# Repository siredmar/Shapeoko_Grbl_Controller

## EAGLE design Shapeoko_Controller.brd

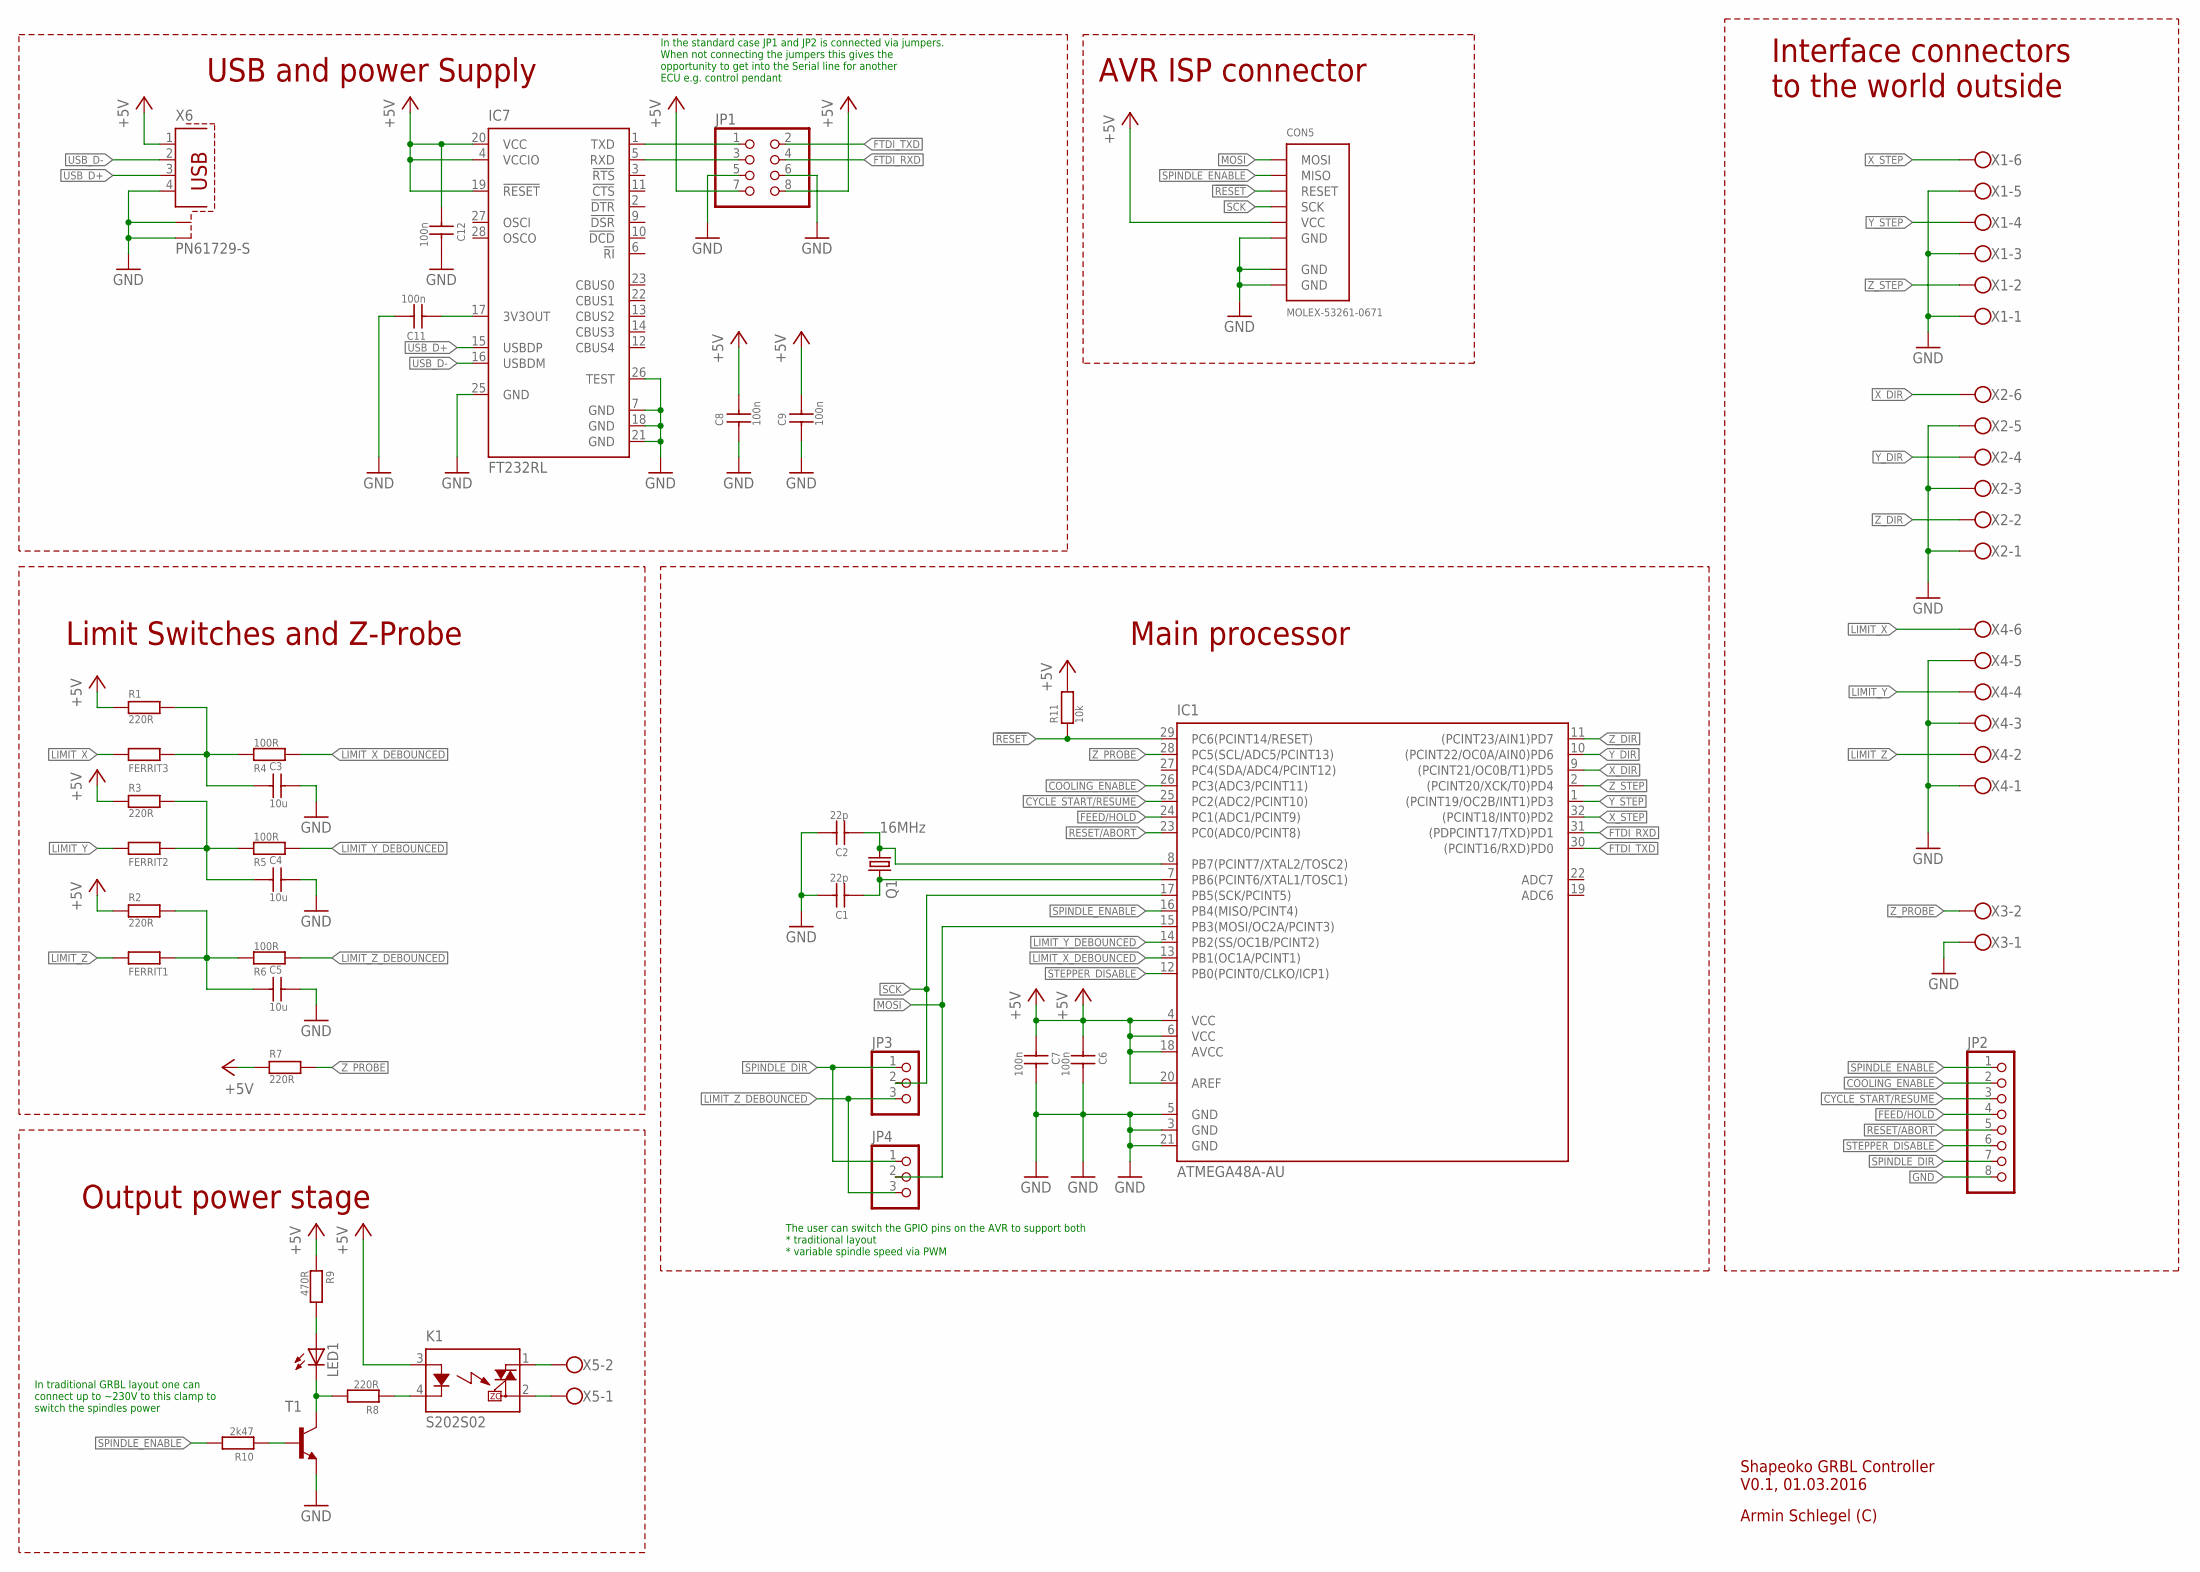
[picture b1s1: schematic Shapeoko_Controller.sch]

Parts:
C1, C2: 22p; C0603
C3, C4, C5: 10u; C0805
C6, C7, C8, C9, C11, C12: 100n; C0603
CON5: MOLEX-53261-0671
FERRIT1, FERRIT2, FERRIT3: R0805
IC1: ATMEGA48A-AU; TQFP32
IC7: FT232RL; SSOP28
JP1: PINHD-2X4; 2X04
JP2: PINHD-1X8; 1X08
JP3, JP4: PINHD-1X3; 1X03
K1: S202S02
LED1: LED3MM
Q1: 16MHz; HC49UP
R1, R2, R3, R7, R8: 220R; R0603
R4, R5, R6: 100R; R0603
R9: 470R; R0603
R10: 2k47; R0603
R11: 10k; R0603
T1: BC847-NPN-SOT23-BEC; SOT23-BEC
X1, X2, X4: W237-136
X3, X5: W237-102
X6: PN61729-S

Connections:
!RESET: CON5.3 (RESET), IC1.29 (PC6(PCINT14/RESET)), R11.1
+5V: C6.1, C7.1, C8.2, C9.2, C12.1, CON5.5 (VCC), IC1.4 (VCC), IC1.6 (VCC), IC1.18 (AVCC), IC1.20 (AREF), IC7.4 (VCCIO), IC7.19 (!RESET), IC7.20 (VCC), JP1.7, JP1.8, K1.3 (A), R1.1, R2.1, R3.1, R7.1, R9.1, R11.2, X6.1
COOLING_ENABLE: IC1.26 (PC3(ADC3/PCINT11)), JP2.2
CYCLE_START/RESUME: IC1.25 (PC2(ADC2/PCINT10)), JP2.3
FEED/HOLD: IC1.24 (PC1(ADC1/PCINT9)), JP2.4
FTDI_3V3OUT: C11.1, IC7.17 (3V3OUT)
FTDI_RXD: IC1.31 ((PDPCINT17/TXD)PD1), JP1.4
FTDI_TXD: IC1.30 ((PCINT16/RXD)PD0), JP1.2
GND: C1.2, C2.2, C3.2, C4.2, C5.2, C6.2, C7.2, C8.1, C9.1, C11.2, C12.2, CON5.6 (GND), CON5.GND@1 (GND), CON5.GND@2 (GND), IC1.3 (GND), IC1.5 (GND), IC1.21 (GND), IC7.7 (GND), IC7.18 (GND), IC7.21 (GND), IC7.25 (GND), IC7.26 (TEST), JP1.5, JP1.6, JP2.8, T1.E, X1.1, X1.3, X1.5, X2.1, X2.3, X2.5, X3.1, X4.1, X4.3, X4.5, X6.4, X6.S1, X6.S2
LIMIT_INT_X: C3.1, FERRIT3.2, R1.2, R4.1
LIMIT_INT_Y: C4.1, FERRIT2.2, R3.2, R5.1
LIMIT_INT_Z: C5.1, FERRIT1.2, R2.2, R6.1
LIMIT_X: FERRIT3.1, X4.6
LIMIT_X_DEBOUNCED: IC1.13 (PB1(OC1A/PCINT1)), R4.2
LIMIT_Y: FERRIT2.1, X4.4
LIMIT_Y_DEBOUNCED: IC1.14 (PB2(SS/OC1B/PCINT2)), R5.2
LIMIT_Z: FERRIT1.1, X4.2
LIMIT_Z_DEBOUNCED: JP3.3, JP4.3, R6.2
MOSI: CON5.1 (MOSI), IC1.15 (PB3(MOSI/OC2A/PCINT3)), JP4.2
unnamed: C2.1, IC1.8 (PB7(PCINT7/XTAL2/TOSC2)), Q1.1
unnamed: C1.1, IC1.7 (PB6(PCINT6/XTAL1/TOSC1)), Q1.2
unnamed: LED1.K (C), R8.2, T1.C
unnamed: LED1.A, R9.2
unnamed: IC7.1 (TXD), JP1.1
unnamed: R10.1, T1.B
unnamed: K1.4 (K), R8.1
unnamed: IC7.5 (RXD), JP1.3
RESET/ABORT: IC1.23 (PC0(ADC0/PCINT8)), JP2.5
SCK: CON5.4 (SCK), IC1.17 (PB5(SCK/PCINT5)), JP3.2
SPINDLE_DIR: JP2.7, JP3.1, JP4.1
SPINDLE_ENABLE: CON5.2 (MISO), IC1.16 (PB4(MISO/PCINT4)), JP2.1, R10.2
SPINDLE_N: K1.2 (DS2), X5.1
SPINDLE_P: K1.1 (DS1), X5.2
STEPPER_DISABLE: IC1.12 (PB0(PCINT0/CLKO/ICP1)), JP2.6
USB_D+: IC7.15 (USBDP), X6.3
USB_D-: IC7.16 (USBDM), X6.2
X_DIR: IC1.9 ((PCINT21/OC0B/T1)PD5), X2.6
X_STEP: IC1.32 ((PCINT18/INT0)PD2), X1.6
Y_DIR: IC1.10 ((PCINT22/OC0A/AIN0)PD6), X2.4
Y_STEP: IC1.1 ((PCINT19/OC2B/INT1)PD3), X1.4
Z_DIR: IC1.11 ((PCINT23/AIN1)PD7), X2.2
Z_PROBE: IC1.28 (PC5(SCL/ADC5/PCINT13)), R7.2, X3.2
Z_STEP: IC1.2 ((PCINT20/XCK/T0)PD4), X1.2

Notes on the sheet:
AVR ISP connector
In the standard case JP1 and JP2 is connected via jumpers. When not connecting the jumpers this gives the opportunity to get into the Serial line for another ECU e.g. control pendant
The user can switch the GPIO pins on the AVR to support both * traditional layout * variable spindle speed via PWM
In traditional GRBL layout one can connect up to ~230V to this clamp to switch the spindles power
USB and power Supply
Limit Switches and Z-Probe
Output power stage
Main processor
Interface connectors to the world outside
Shapeoko GRBL Controller V0.1, 01.03.2016
Armin Schlegel (C)

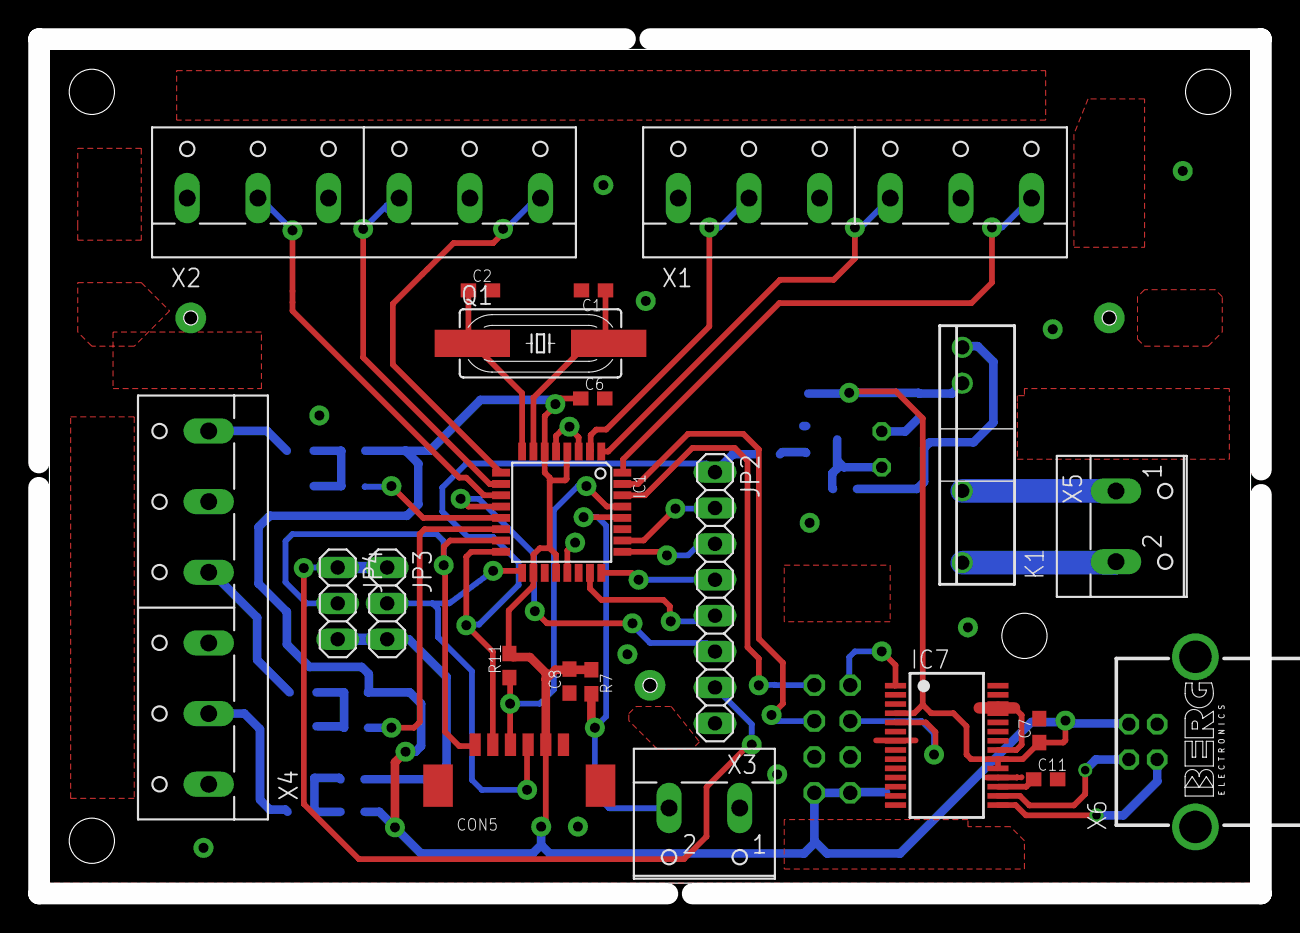
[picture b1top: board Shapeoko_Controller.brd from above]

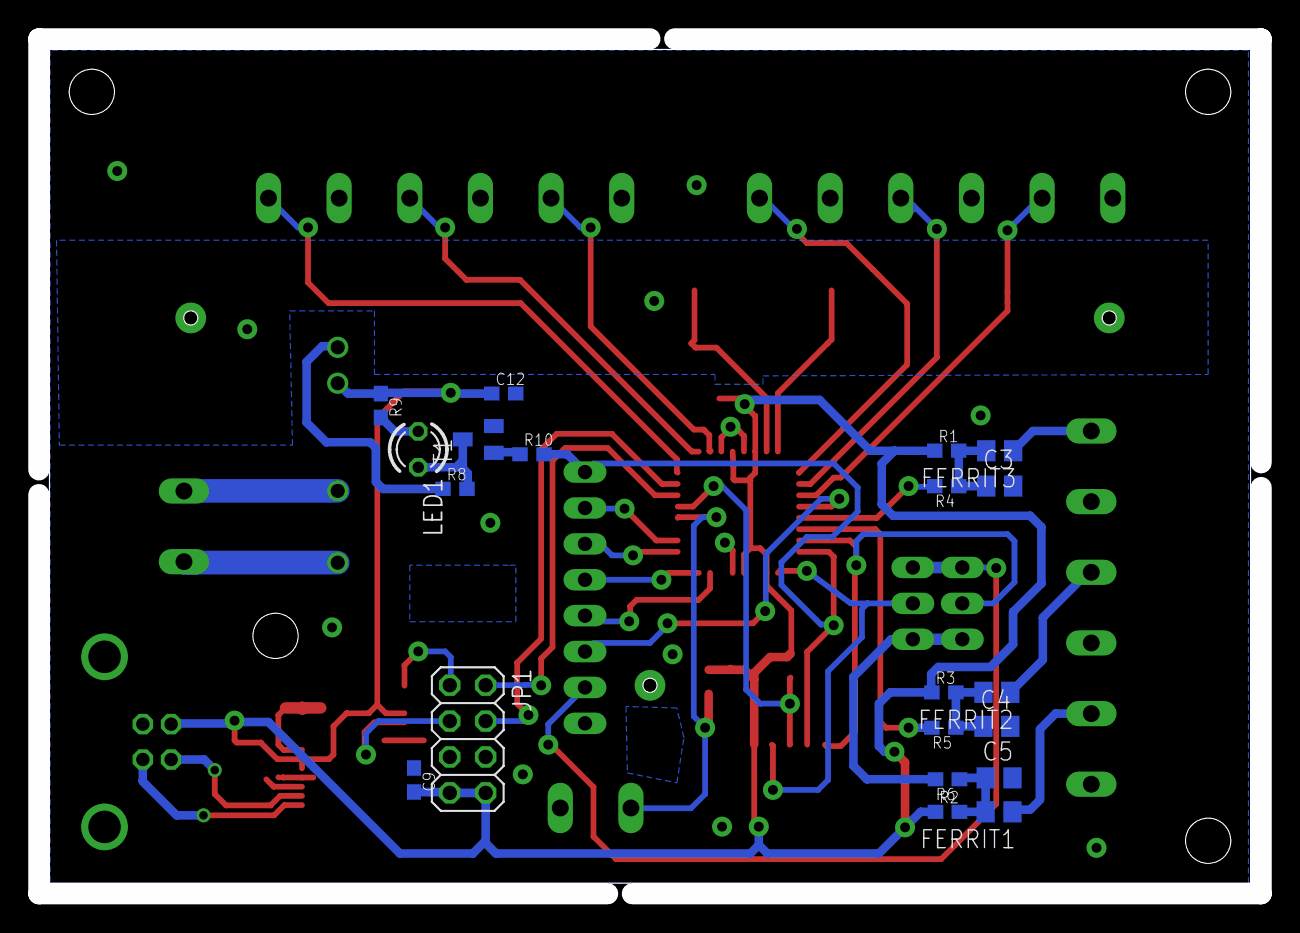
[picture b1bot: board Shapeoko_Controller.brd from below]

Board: 2 copper layers, 86.5 x 60.5 mm, 42 parts (20 on the bottom side), 43 nets.

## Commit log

2016-03-31 First version of Shapeoko GRBL Controller
